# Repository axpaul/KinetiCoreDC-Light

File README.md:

# KinetiCoreDC Light

🌐 **Langue / Language :** [🇫🇷 Français](README.md) | [🇬🇧 English](README.en.md)

---

**KinetiCoreDC Light** est la **version minimale et compacte** du contrôleur de moteur DC durci **[KinetiCoreDC](https://github.com/axpaul/KinetiCoreDC)**. Conçue pour réduire au maximum l'encombrement PCB et le coût de nomenclature (BOM), cette variante conserve l'étage de puissance protégé, le pont en H `DRV8874`, les entrées de commande opto-isolées et le retour d'encodeur incrémental, tout en supprimant les bus périphériques encombrants de la version complète. Développé par **Paul Miailhe** pour **Berry Rocket**.

© 2025/2026 - **Paul Miailhe** (*Berry Rocket*).  
This material is licensed under the **CERN Open Hardware Licence Version 2 - Strongly Reciprocal (CERN-OHL-S)**. $\rightarrow$ [LICENSE](LICENSE)

---

## 1. Différences avec le dépôt officiel `KinetiCoreDC`

Cette édition **Light** cible les intégrations embarquées à fort contrainte de volume où un pilotage PWM/RC local avec retour incrémental suffit :

| Fonction / Bloc | [KinetiCoreDC (Officiel)](https://github.com/axpaul/KinetiCoreDC) | KinetiCoreDC Light (Ce dépôt) |
| :--- | :---: | :---: |
| **Protection alim (`LTC4365` + 2× `SiS412DN`) & LDO `3,3 V`** | ✅ Inclus | ✅ **Conservé** |
| **Driver moteur `DRV8874PWPR` ($6\text{ A}$ crête) + mesure `IPROPI`** | ✅ Inclus | ✅ **Conservé** |
| **Entrées opto-isolées PWM / GPIO (`2× TLP2310`)** | ✅ Inclus | ✅ **Conservé** (voie principale + redondante) |
| **Encodeur quadrature incrémental A/B (`TIM3` + Schmitt)** | ✅ Inclus | ✅ **Conservé** |
| **Fins de course (`2×` contact sec filtré + Schmitt)** | ✅ Inclus | ✅ **Conservé** |
| **Debug SWD + UART VCP (`Tag-Connect TC2070`)** | ✅ Inclus | ✅ **Conservé** |
| **IHM embarquée (LED RGB, buzzer piézo, LEDs sens moteur)** | ✅ Inclus | ✅ **Conservé** |
| **Sortie puissance moteur** | Connecteur `XT30PW-M` | 🔧 **Pads à souder directs** (`OUTA` / `OUTB`) |
| **Bus terrain différentiel RS-485 (`THVD1400D` + `SM712`)** | ✅ Inclus | ❌ **Retiré** (gain de surface PCB) |
| **Port capteur absolu SPI2 / I²C1 (`AS5047P` / `AS5600`)** | ✅ Inclus | ❌ **Retiré** (gain de surface PCB) |

---

## 2. Vue d'ensemble & Applications

Articulée autour d'un microcontrôleur **STM32G070CBT6** (ARM Cortex-M0+ @ $64\text{ MHz}$, horloge interne HSI) et d'un pont en H intégré **DRV8874PWPR**, la carte intègre l'essentiel de l'électronique de puissance, de protection et de conditionnement nécessaire au pilotage précis d'un actionneur DC :

- **Actionneur PWM / RC durci ou redondant :** Pilotage par consigne PWM ou impulsion RC ($1\text{–}2\text{ ms}$) via deux entrées opto-isolées (`TLP2310`) autorisant une voie de commande secondaire de secours.
- **Asservissement compact en boucle fermée :** Régulation PID en position, vitesse ou couple grâce au décodage quadrature matériel (`TIM3`), à la prise d'origine (*homing*) sur butées mécaniques et à la mesure de courant moteur (`IPROPI`).

---

## 3. Caractéristiques électriques

L'étage d'entrée est dimensionné pour une alimentation sur batterie **LiPo 2S ou 3S** (ou source DC régulée). Un contrôleur **LTC4365TS8** associé à deux MOSFETs N-Channel tête-bêche (**SiS412DN**) assure la coupure matérielle en cas de sous-tension, surtension ou inversion de polarité, tandis qu'une diode TVS **SMBJ15CA** protège le régulateur $+3{,}3\text{ V}$ contre les transitoires.

| Paramètre | Symbole | Min | Typ | Max | Unité | Conditions / Notes |
| :--- | :--- | :---: | :---: | :---: | :---: | :--- |
| **Tension d'entrée** | $V_{\text{IN}}$ | $5{,}90$ | $7{,}4\text{–}11{,}1$ | **$14{,}75$** | $\text{V}$ | Compatible LiPo 2S ($8{,}4\text{ V}$) et 3S ($12{,}6\text{ V}$) |
| **Tenue inversion polarité** | $V_{\text{REV}}$ | **$-40$** | — | — | $\text{V}$ | Blocage par N-MOSFETs tête-bêche |
| **Seuil sous-tension (coupure)** | $V_{\text{UVLO}}$ | — | $5{,}90$ | — | $\text{V}$ | Enclenchement à $6{,}20\text{ V}$ (config. défaut) |
| **Seuil surtension (coupure)** | $V_{\text{OVLO}}$ | — | **$14{,}75$** | — | $\text{V}$ | Réarmement à $14{,}01\text{ V}$ (TVS `SMBJ15CA`) |
| **Courant moteur régulé** | $I_{\text{TRIP}}$ | — | **$2{,}6$** | **$2{,}6$** | $\text{A}$ | $V_{\text{REF}} = 2{,}50\text{ V}$, $R_{\text{IPROPI}} = 2{,}49\text{ k}\Omega$ |
| **Courant moteur crête** | $I_{\text{PEAK}}$ | — | — | **$6{,}0$** | $\text{A}$ | Limite silicium `DRV8874` |
| **Puissance d'entrée** | $P_{\text{IN}}$ | — | $32{,}8$ | $38{,}4$ | $\text{W}$ | À $I_{\text{TRIP}} = 2{,}6\text{ A}$ (jusqu'à $88{,}5\text{ W}$ crête à $6\text{ A}$) |
| **Rail logique** | $V_{\text{3V3}}$ | $3{,}28$ | $3{,}30$ | $3{,}32$ | $\text{V}$ | Précision $\pm 0{,}4\text{ \%}$ (`MCP1703A`, boîtier SOT-223) |
| **Courant disponible $+3{,}3\text{ V}$** | $I_{\text{OUT(3V3)}}$ | — | — | **$250$** | $\text{mA}$ | Total carte ($\approx 50\text{ mA}$) + encodeur externe |
| **Courant de veille** | $I_{\text{SHDN}}$ | — | — | **$< 10$** | $\mu\text{A}$ | Broche `SHDN_EXT` tirée à `GND` |

> **Ajustement des seuils :** La fenêtre de protection UVLO/OVLO peut être adaptée à un profil batterie spécifique (LiPo 2S dédié $6{,}45\text{–}10{,}84\text{ V}$, LiPo 3S dédié $9{,}15\text{–}14{,}28\text{ V}$ ou pile 9V) via le pont diviseur du `LTC4365` sur la feuille `Power.kicad_sch`. Le seuil de courant $I_{\text{TRIP}}$ est également ajustable jusqu'à $6\text{ A}$ via `R_IPROPI`.

---

## 4. Interfaces & Connectique

Toutes les entrées/sorties externes conservées bénéficient des mêmes protections contre les décharges électrostatiques (ESD), les inversions de câblage et le bruit de découpage moteur ($32\text{ kHz}$). Le départ d'alimentation $+3{,}3\text{ V}$ vers l'encodeur (`J10`) est protégé par une résistance série de $22\ \Omega$, tandis que les signaux logiques sont filtrés matériellement puis remis en forme par des triggers de Schmitt (**SN74LVC2G14DBV**).

| Connecteur | Interface | Signal / Protocole | Conditionnement & Protection | Compatibilité |
| :--- | :--- | :--- | :--- | :--- |
| **`J2`** | `XT30PW-M` (2 pts) | Puissance entrée $V_{\text{IN}}$ | TVS `SMBJ15CA`, N-MOSFETs `SiS412DN` | Batterie LiPo 2S–3S ($15\text{ A}$ cont.) |
| **`J3` / `J4`** | Pads à souder (`1×1`) | Sorties moteur `OUTA` / `OUTB` | LEDs antiparallèles sens/PWM ($2\text{ k}\Omega$) | Moteur DC à balais (fils directs) |
| **`J7` / `J8`** | `JST-GH` (2 pts) | $2\times$ PWM / GPIO isolés ($3{,}3\text{–}5\text{ V}$) | Optocoupleurs `TLP2310`, clamp inverse `SMF6.0A` | Consigne PWM/RC, voie redondante |
| **`J10`** | `JST-GH` (4 pts) | Encodeur quadrature A/B ($3{,}3\text{–}5\text{ V}$) | `USBLC6-2SC6`, $+3{,}3\text{ V}$ ($22\ \Omega$), RC ($160\text{ kHz}$) + Schmitt | Encodeurs incrémentaux à effet Hall |
| **`J11` / `J5`** | `JST-GH` (2 pts) | $2\times$ Fins de course (`TRIG1` / `TRIG2`) | Pull-up $2{,}2\text{ k}\Omega$, RC ($160\text{ Hz}$) + Schmitt | Butées mécaniques Min / Max |
| **`J9`** | `JST-GH` (3 pts) | Activation carte (`SHDN_EXT`) | Pull-up $510\text{ k}\Omega$ vers $V_{\text{IN}}$ (`LTC4365`) | Interrupteur marche / veille |
| **`J6`** | `JST-GH` (2 pts) | Sortie défaut alim (`NFAULT_EXT`) | Drain ouvert actif bas + $22\ \Omega$ (`LTC4365`) | Supervision système hôte |
| **`J1`** | `TC2070-NL` (14 pts) | SWD + NRST + UART VCP (`USART3`) | Empreinte sans composants (STDC14) | ST-LINK/V3 (flash & debug) |

---

## 5. Brochage MCU (`STM32G070CBT6` — LQFP48)

| Bloc fonctionnel | Signal | Broche | Périphérique | Fonction |
| :--- | :--- | :---: | :--- | :--- |
| **Driver Moteur** | `PH/IN2_MCU` | `PA8` (28) | `TIM1_CH1` | Direction (`PH`) ou PWM secondaire |
| | `EN/IN1_MCU` | `PA9` (29) | `TIM1_CH2` | PWM principale moteur ($32\text{ kHz}$) |
| | `NSLEEP_MCU` | `PC6` (30) | `GPIO_Output` | Activation / Veille du pont en H |
| | `PMODE_MCU` | `PC7` (31) | `GPIO_Output` | Mode `PH/EN` (`0`) ou `PWM` (`1`) |
| | `NFAULT_MCU` | `PA10` (32) | `GPIO_EXTI10` | Interruption défaut driver (front descendant) |
| | `IPROPI_MCU` | `PB10` (22) | `ADC1_IN11` | Lecture courant moteur ($1{,}13\text{ V/A}$, filtre RC) |
| **Supervision** | `ADC_VM` | `PB2` (21) | `ADC1_IN10` | Mesure tension d'entrée $V_M$ |
| **Encodeur** | `TIM_ENC_A` / `B` | `PA6` (17), `PA7` (18) | `TIM3_CH1/CH2` | Décodage quadrature matériel X4 |
| **Optocoupleurs** | `OPTO1_MCU` / `OPTO2_MCU` | `PB14` (26), `PB15` (27) | `TIM15_CH1/CH2` | Input Capture PWM / Consigne redondante |
| **Fins de course** | `TRIG1_MCU` / `TRIG2_MCU` | `PD2` (40), `PD3` (41) | `GPIO_EXTI2/EXTI3` | Interruptions butées (front montant) |
| **IHM** | `BLUE` / `RED` / `GREEN` | `PC13`, `PC14`, `PC15` | `GPIO_Output` | LED RGB 8 couleurs (anode commune, actif bas) |
| | `BUZZER_MCU` | `PA4` (15) | `TIM14_CH1` | Signal piézo PWM $4\text{ kHz}$ |
| **Debug** | `SWDIO` / `SWCLK` | `PA13` (35), `PA14` (36) | `SYS_SWD` | Programmation et débogage |
| | `VPC_TX` / `VPC_RX` | `PA5` (16), `PB0` (19) | `USART3_TX/RX` | Console série virtuelle de diagnostic |

---

## 6. Architecture KiCad & Structure du dépôt

Le projet est conçu sous **KiCad 10.0** autour d'une feuille racine et de trois sous-feuilles hiérarchiques allégées, accompagnées du fichier de configuration **STM32CubeMX** (`KinetiCoreDC.ioc`) :

```text
KinetiCoreDC-Light/
├── KinetiCoreDC.kicad_pro       # Projet KiCad 10.0
├── KinetiCoreDC.kicad_sch       # Feuille 1/4 : MCU STM32G070CBT6 & hiérarchie
├── Interface.kicad_sch          # Feuille 2/4 : Optocoupleurs, encodeur quadrature, butées
├── Power.kicad_sch              # Feuille 3/4 : LTC4365, LDO 3.3V, DRV8874, RGB, buzzer
├── Connector.kicad_sch          # Feuille 4/4 : XT30 entrée, pads moteur, JST-GH, Tag-Connect
├── KinetiCoreDC.kicad_pcb       # Routage PCB compact
├── KinetiCoreDC.ioc             # Configuration matérielle STM32CubeMX
├── Datasheet/                   # Fiches techniques des composants
├── lib/                         # Symboles, empreintes et modèles 3D locaux
├── README.md                    # Documentation française
├── README.en.md                 # Documentation anglaise
└── LICENSE                      # Licence CERN-OHL-S-2.0

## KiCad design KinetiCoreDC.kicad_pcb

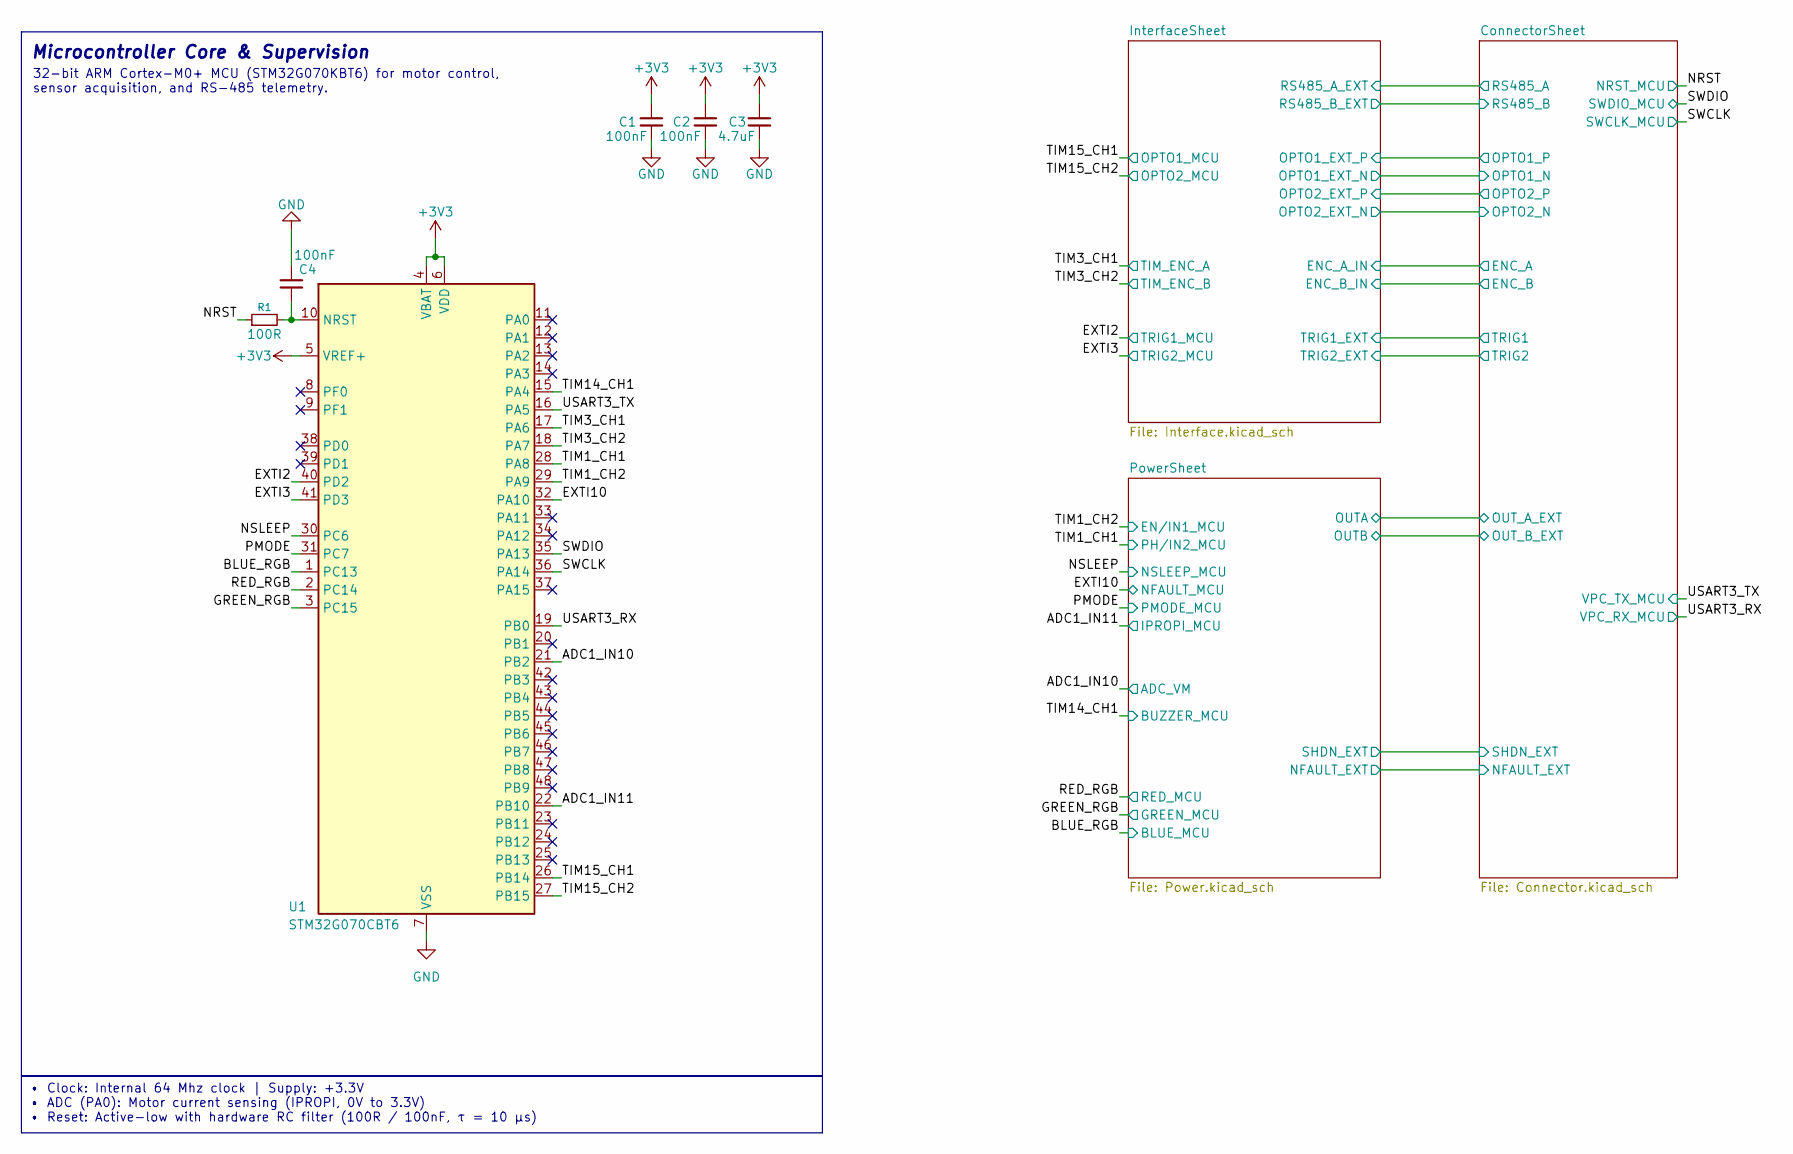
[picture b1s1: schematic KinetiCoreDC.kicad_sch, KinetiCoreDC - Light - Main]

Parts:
C1, C2, C4: 100nF; C_0603_1608Metric
C3: 4.7uF; C_0603_1608Metric
R1: 100R; R_0603_1608Metric
U1: STM32G070CBT6; LQFP-48_7x7mm_P0.5mm

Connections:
+3V3: C1.1, C2.1, C3.1, U1.4 (VBAT), U1.5 (VREF+), U1.6 (VDD); also elsewhere on the board
/ADC1_IN10: U1.21 (PB2); also elsewhere on the board
/ADC1_IN11: U1.22 (PB10); also elsewhere on the board
/BLUE_RGB: U1.1 (PC13); also elsewhere on the board
/EXTI2: U1.40 (PD2); also elsewhere on the board
/EXTI3: U1.41 (PD3); also elsewhere on the board
/EXTI10: U1.32 (PA10); also elsewhere on the board
/GREEN_RGB: U1.3 (PC15); also elsewhere on the board
/NRST: R1.1; also elsewhere on the board
/NSLEEP: U1.30 (PC6); also elsewhere on the board
/PMODE: U1.31 (PC7); also elsewhere on the board
/RED_RGB: U1.2 (PC14); also elsewhere on the board
/SWCLK: U1.36 (PA14); also elsewhere on the board
/SWDIO: U1.35 (PA13); also elsewhere on the board
/TIM1_CH1: U1.28 (PA8); also elsewhere on the board
/TIM1_CH2: U1.29 (PA9); also elsewhere on the board
/TIM3_CH1: U1.17 (PA6); also elsewhere on the board
/TIM3_CH2: U1.18 (PA7); also elsewhere on the board
/TIM14_CH1: U1.15 (PA4); also elsewhere on the board
/TIM15_CH1: U1.26 (PB14); also elsewhere on the board
/TIM15_CH2: U1.27 (PB15); also elsewhere on the board
/USART3_RX: U1.19 (PB0); also elsewhere on the board
/USART3_TX: U1.16 (PA5); also elsewhere on the board
GND: C1.2, C2.2, C3.2, C4.2, U1.7 (VSS); also elsewhere on the board
unnamed: C4.1, R1.2, U1.10 (NRST)

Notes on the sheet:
Microcontroller Core & Supervision
32-bit ARM Cortex-M0+ MCU (STM32G070KBT6) for motor control, sensor acquisition, and RS-485 telemetry.
• Clock: Internal 64 Mhz clock | Supply: +3.3V • ADC (PA0): Motor current sensing (IPROPI, 0V to 3.3V) • Reset: Active-low with hardware RC filter (100R / 100nF, τ = 10 µs)

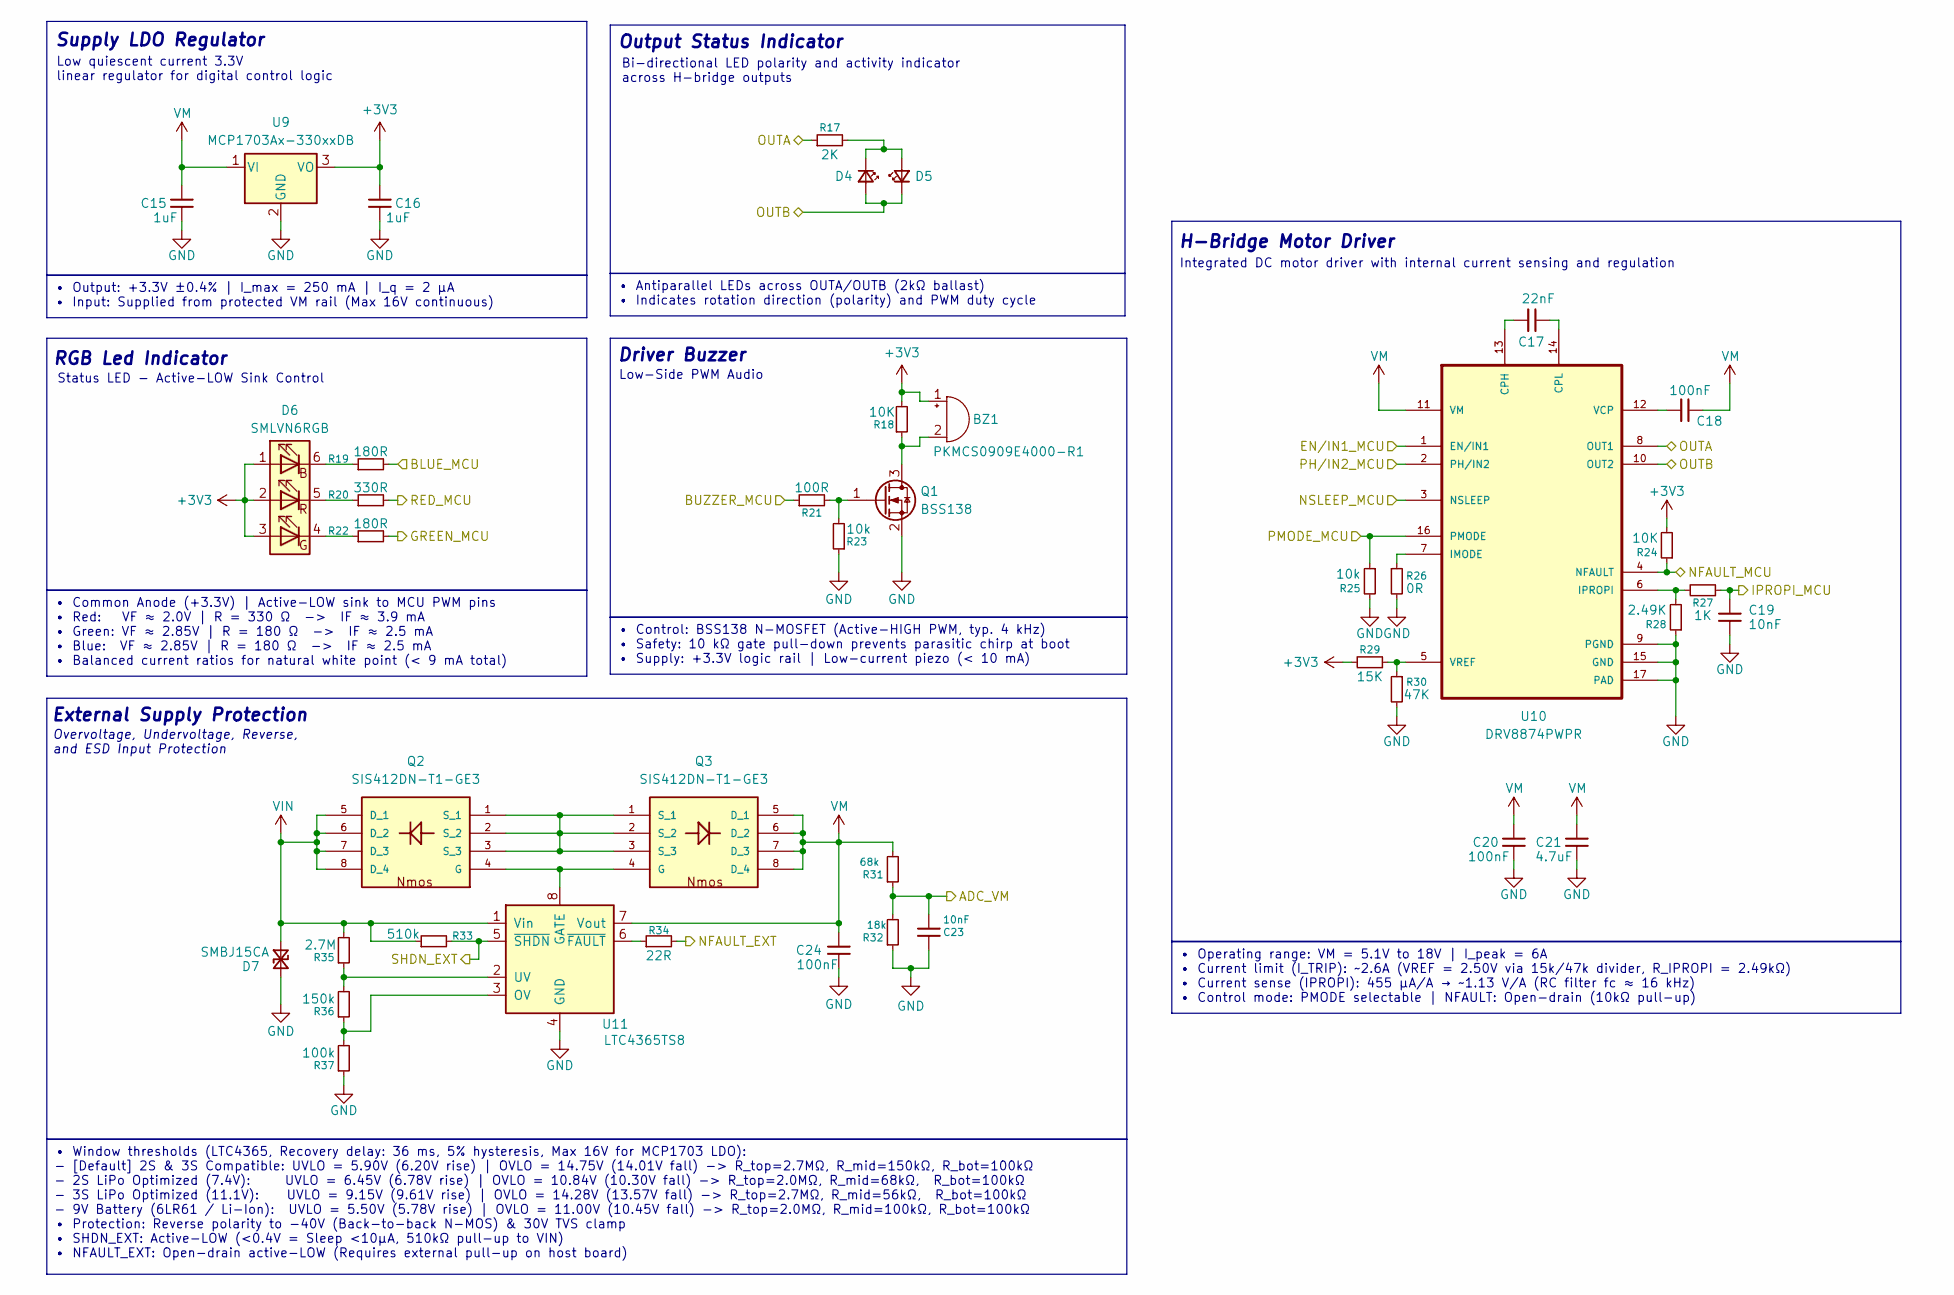
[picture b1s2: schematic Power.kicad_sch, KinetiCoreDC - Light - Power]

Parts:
BZ1: PKMCS0909E4000-R1; Buzzer_Murata_PKMCS0909E
C15, C16: 1uF; C_0805_2012Metric
C17: 22nF; C_0603_1608Metric
C18, C24: 100nF; C_0603_1608Metric
C19, C23: 10nF; C_0603_1608Metric
C20: 100nF; C_0805_2012Metric
C21: 4.7uF; C_0805_2012Metric
D4, D5: LED_Small; LED_0603_1608Metric
D6: SMLVN6RGB; LED_ROHM_SMLVN6
D7: SMBJ15CA; D_SMA
Q1: BSS138; SOT-23
Q2, Q3: SIS412DN-T1-GE3; POWERPAK-1212-8; MOUSER_PART_NUMBER 781-SIS412DN-T1-GE3
R17: 2K; R_0603_1608Metric
R18, R24: 10K; R_0603_1608Metric
R19, R22: 180R; R_0603_1608Metric
R20: 330R; R_0603_1608Metric
R21: 100R; R_0603_1608Metric
R23, R25: 10k; R_0603_1608Metric
R26: 0R; R_0603_1608Metric
R27: 1K; R_0603_1608Metric
R28: 2.49K; R_0603_1608Metric
R29: 15K; R_0603_1608Metric
R30: 47K; R_0603_1608Metric
R31: 68k; R_0603_1608Metric
R32: 18k; R_0603_1608Metric
R33: 510k; R_0603_1608Metric
R34: 22R; R_0603_1608Metric
R35: 2.7M; R_0603_1608Metric
R36: 150k; R_0603_1608Metric
R37: 100k; R_0603_1608Metric
U9: MCP1703Ax-330xxDB; SOT-223-3_TabPin2
U10: DRV8874PWPR; SOP65P640X120-17N
U11: LTC4365TS8; TSOT-23-8

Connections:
+3V3: BZ1.1 (+), C16.1, D6.1 (BA), D6.2 (RA), D6.3 (GA), R18.2, R24.2, R29.2, U9.3 (VO); also elsewhere on the board
/ADC1_IN10: C23.2, R31.1, R32.2; also elsewhere on the board
/ADC1_IN11: C19.2, R27.1; also elsewhere on the board
/BLUE_RGB: R19.2; also elsewhere on the board
/ConnectorSheet/NFAULT_EXT: R34.2; also elsewhere on the board
/ConnectorSheet/OUT_A_EXT: R17.1, U10.8 (OUT1); also elsewhere on the board
/ConnectorSheet/OUT_B_EXT: D4.2 (A), D5.1 (K), U10.10 (OUT2); also elsewhere on the board
/ConnectorSheet/SHDN_EXT: R33.2, U11.5 (~SHDN); also elsewhere on the board
/EXTI10: R24.1, U10.4 (NFAULT); also elsewhere on the board
/GREEN_RGB: R22.2; also elsewhere on the board
/NSLEEP: U10.3 (NSLEEP); also elsewhere on the board
/PMODE: R25.1, U10.16 (PMODE); also elsewhere on the board
/RED_RGB: R20.2; also elsewhere on the board
/TIM1_CH1: U10.2 (PH/IN2); also elsewhere on the board
/TIM1_CH2: U10.1 (EN/IN1); also elsewhere on the board
/TIM14_CH1: R21.1; also elsewhere on the board
GND: C15.2, C16.2, C19.1, C20.2, C21.2, C23.1, C24.2, D7.2 (A2), Q1.2 (S), R23.1, R25.2, R26.2, R28.1, R30.2, R32.1, R37.1, U9.2 (GND), U10.9 (PGND), U10.15 (GND), U10.17 (PAD), U11.4 (GND); also elsewhere on the board
unnamed: BZ1.2 (-), Q1.3 (D), R18.1
unnamed: D4.1 (K), D5.2 (A), R17.2
unnamed: D6.6 (BK), R19.1
unnamed: D6.4 (GK), R22.1
unnamed: D6.5 (RK), R20.1
unnamed: Q1.1 (G), R21.2, R23.2
unnamed: Q2.4 (G), Q3.4 (G), U11.8 (GATE)
unnamed: Q2.1 (S_1), Q2.2 (S_2), Q2.3 (S_3), Q3.1 (S_1), Q3.2 (S_2), Q3.3 (S_3)
unnamed: C17.1, U10.13 (CPH)
unnamed: C17.2, U10.14 (CPL)
unnamed: R26.1, U10.7 (IMODE)
unnamed: R27.2, R28.2, U10.6 (IPROPI)
unnamed: C18.1, U10.12 (VCP)
unnamed: R29.1, R30.1, U10.5 (VREF)
unnamed: R36.1, R37.2, U11.3 (OV)
unnamed: R35.1, R36.2, U11.2 (UV)
unnamed: R34.1, U11.6 (~FAULT)
VIN: D7.1 (A1), Q2.5 (D_1), Q2.6 (D_2), Q2.7 (D_3), Q2.8 (D_4), R33.1, R35.2, U11.1 (Vin); also elsewhere on the board
VM: C15.1, C18.2, C20.1, C21.1, C24.1, Q3.5 (D_1), Q3.6 (D_2), Q3.7 (D_3), Q3.8 (D_4), R31.2, U9.1 (VI), U10.11 (VM), U11.7 (Vout)

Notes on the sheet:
H-Bridge Motor Driver
RGB Led Indicator
Low quiescent current 3.3V linear regulator for digital control logic
Low-Side PWM Audio
Output Status Indicator
Driver Buzzer
Supply LDO Regulator
Overvoltage, Undervoltage, Reverse, and ESD Input Protection
Integrated DC motor driver with internal current sensing and regulation
External Supply Protection
Bi-directional LED polarity and activity indicator across H-bridge outputs
Status LED - Active-LOW Sink Control
• Control: BSS138 N-MOSFET (Active-HIGH PWM, typ. 4 kHz) • Safety: 10 kΩ gate pull-down prevents parasitic chirp at boot • Supply: +3.3V logic rail | Low-current piezo (< 10 mA)
• Window thresholds (LTC4365, Recovery delay: 36 ms, 5% hysteresis, Max 16V for MCP1703 LDO): - [Default] 2S & 3S Compatible: UVLO = 5.90V (6.20V rise) | OVLO = 14.75V (14.01V fall) -> R_top=2.7MΩ, R_mid=150kΩ, R_bot=100kΩ - 2S LiPo Optimized (7.4V): UVLO = 6.45V (6.78V rise) | OVLO = 10.84V (10.30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
• Output: +3.3V ±0.4% | I_max = 250 mA | I_q = 2 µA • Input: Supplied from protected VM rail (Max 16V continuous)
• Antiparallel LEDs across OUTA/OUTB (2kΩ ballast) • Indicates rotation direction (polarity) and PWM duty cycle
• Operating range: VM = 5.1V to 18V | I_peak = 6A • Current limit (I_TRIP): ~2.6A (VREF = 2.50V via 15k/47k divider, R_IPROPI = 2.49kΩ) • Current sense (IPROPI): 455 µA/A → ~1.13 V/A (RC filter fc ≈ 16 kHz) • Control mode: PMODE selectable | NFAULT: Open-drain (10kΩ pull-up)
• Common Anode (+3.3V) | Active-LOW sink to MCU PWM pins • Red: VF ≈ 2.0V | R = 330 Ω -> IF ≈ 3.9 mA • Green: VF ≈ 2.85V | R = 180 Ω -> IF ≈ 2.5 mA • Blue: VF ≈ 2.85V | R = 180 Ω -> IF ≈ 2.5 mA • Balanced current ratios for natural white point (< 9 mA total)

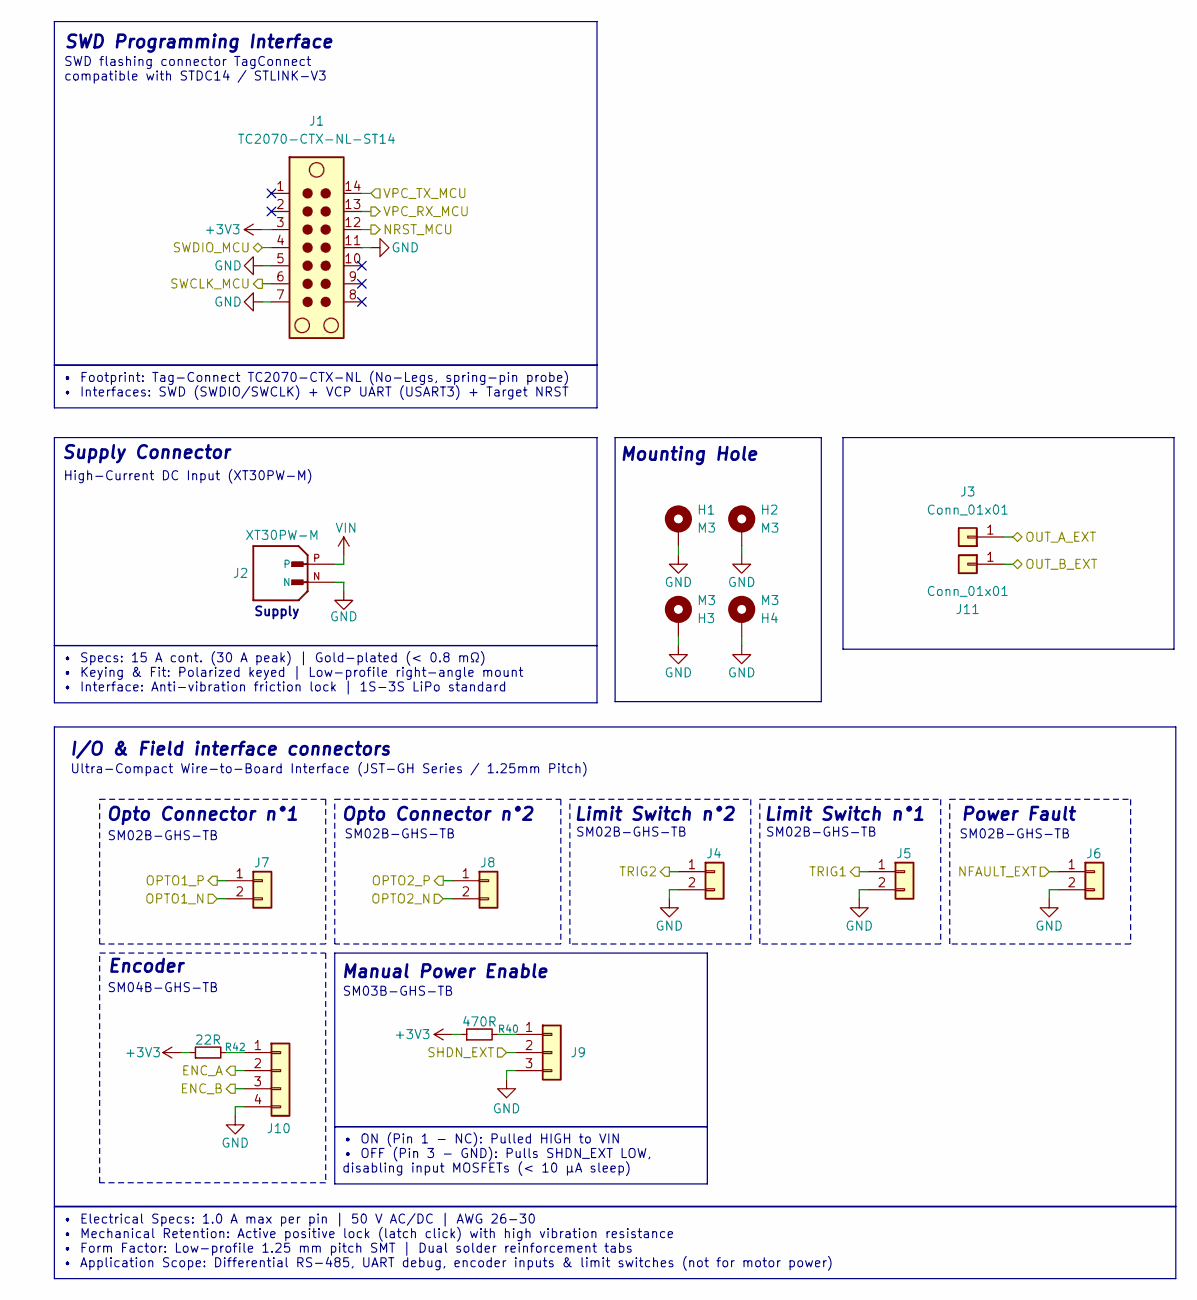
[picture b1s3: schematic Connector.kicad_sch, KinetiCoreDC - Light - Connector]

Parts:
H1, H2, H3, H4: M3; MountingHole_3.2mm_M3_DIN965_Pad_TopBottom
J1: TC2070-CTX-NL-ST14; Tag-Connect_TC2070-IDC-FP_2x07_P1.27mm_Vertical
J2: XT30PW-M; AMASS_XT30PW-M; PARTREV 1.2
J3, J11: Conn_01x01; SolderWirePad_1x01_SMD_4x8mm
J4, J5, J6, J7: SM02B-GHS-TB; JST_GH_SM02B-GHS-TB_1x02-1MP_P1.25mm_Horizontal
J8: BM02B-GHS-TBT; JST_GH_SM02B-GHS-TB_1x02-1MP_P1.25mm_Horizontal
J9: SM03B-GHS-TB; JST_GH_SM03B-GHS-TB_1x03-1MP_P1.25mm_Horizontal
J10: SM04B-GHS-TB; JST_GH_SM04B-GHS-TB_1x04-1MP_P1.25mm_Horizontal
R40: 470R; R_0603_1608Metric
R42: 22R; R_0603_1608Metric

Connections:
+3V3: J1.3, R40.1, R42.1; also elsewhere on the board
/ConnectorSheet/ENC_A: J10.2; also elsewhere on the board
/ConnectorSheet/ENC_B: J10.3; also elsewhere on the board
/ConnectorSheet/NFAULT_EXT: J6.1; also elsewhere on the board
/ConnectorSheet/OPTO1_N: J7.2; also elsewhere on the board
/ConnectorSheet/OPTO1_P: J7.1; also elsewhere on the board
/ConnectorSheet/OPTO2_N: J8.2; also elsewhere on the board
/ConnectorSheet/OPTO2_P: J8.1; also elsewhere on the board
/ConnectorSheet/OUT_A_EXT: J3.1 (Pin_1_1); also elsewhere on the board
/ConnectorSheet/OUT_B_EXT: J11.1 (Pin_1_1); also elsewhere on the board
/ConnectorSheet/SHDN_EXT: J9.2; also elsewhere on the board
/ConnectorSheet/TRIG1: J5.1; also elsewhere on the board
/ConnectorSheet/TRIG2: J4.1; also elsewhere on the board
/NRST: J1.12; also elsewhere on the board
/SWCLK: J1.6; also elsewhere on the board
/SWDIO: J1.4; also elsewhere on the board
/USART3_RX: J1.13; also elsewhere on the board
/USART3_TX: J1.14; also elsewhere on the board
GND: H1.1 (1_1), H2.1 (1_1), H3.1 (1_1), H4.1 (1_1), J1.5, J1.7, J1.11, J2.N, J4.2, J5.2, J6.2, J9.3, J10.4; also elsewhere on the board
unnamed: J9.1, R40.2
unnamed: J10.1, R42.2
VIN: J2.P; also elsewhere on the board

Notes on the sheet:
Limit Switch n°1
Encoder
Power Fault
I/O & Field interface connectors
SM03B-GHS-TB
Opto Connector n°1
High-Current DC Input (XT30PW-M)
SM02B-GHS-TB
SWD flashing connector TagConnect compatible with STDC14 / STLINK-V3
Limit Switch n°2
Opto Connector n°2
Mounting Hole
SM04B-GHS-TB
Manual Power Enable
Ultra-Compact Wire-to-Board Interface (JST-GH Series / 1.25mm Pitch)
Supply Connector
SWD Programming Interface
Supply
• Footprint: Tag-Connect TC2070-CTX-NL (No-Legs, spring-pin probe) • Interfaces: SWD (SWDIO/SWCLK) + VCP UART (USART3) + Target NRST
• Electrical Specs: 1.0 A max per pin | 50 V AC/DC | AWG 26-30 • Mechanical Retention: Active positive lock (latch click) with high vibration resistance • Form Factor: Low-profile 1.25 mm pitch SMT | Dual solder reinforcement tabs • Application Scope: Differential RS-485, UART debug, encoder inputs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
• Specs: 15 A cont. (30 A peak) | Gold-plated (< 0.8 mΩ) • Keying & Fit: Polarized keyed | Low-profile right-angle mount • Interface: Anti-vibration friction lock | 1S-3S LiPo standard
• ON (Pin 1 - NC): Pulled HIGH to VIN • OFF (Pin 3 - GND): Pulls SHDN_EXT LOW, disabling input MOSFETs (< 10 µA sleep)

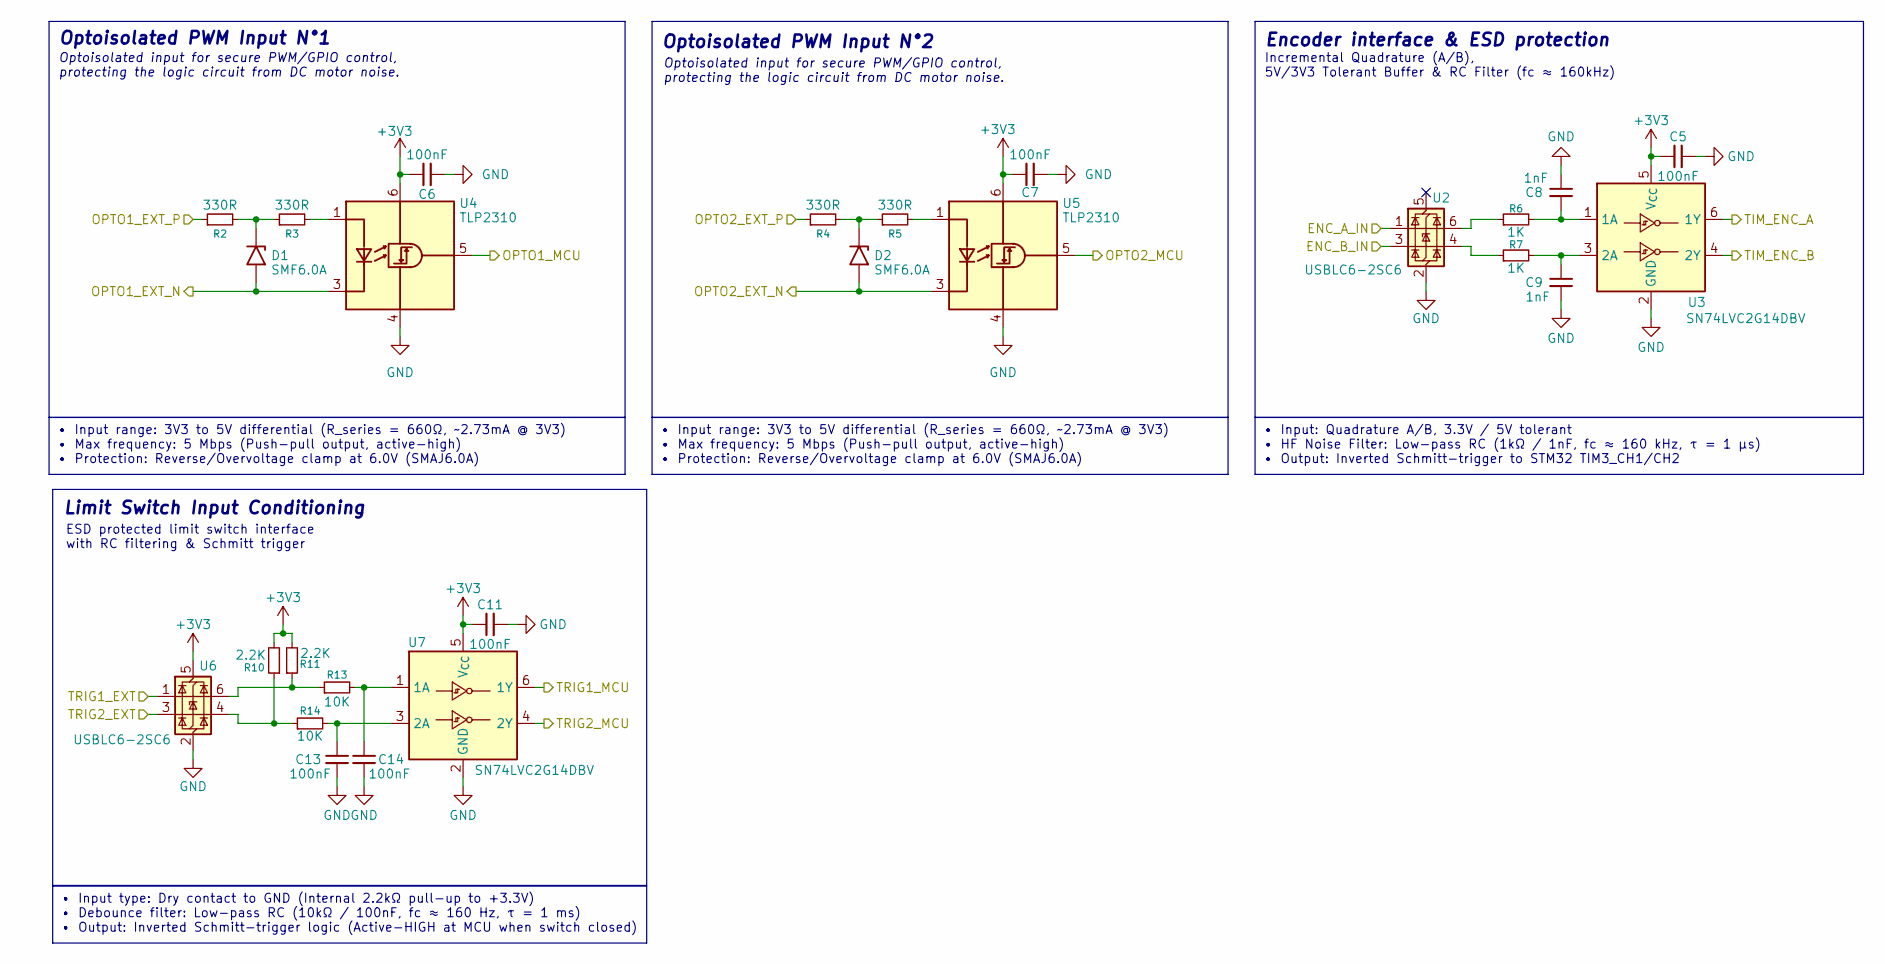
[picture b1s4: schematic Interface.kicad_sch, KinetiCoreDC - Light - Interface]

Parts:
C5, C6, C7, C11, C13, C14: 100nF; C_0603_1608Metric
C8, C9: 1nF; C_0603_1608Metric
D1, D2: SMF6.0A; D_SOD-123F
R2, R3, R4, R5: 330R; R_0603_1608Metric
R6, R7: 1K; R_0603_1608Metric
R10, R11: 2.2K; R_0603_1608Metric
R13, R14: 10K; R_0603_1608Metric
U2, U6: USBLC6-2SC6; SOT-23-6
U3, U7: SN74LVC2G14DBV; SOT-23-6
U4, U5: TLP2310; SO-5-6_4.55x3.7mm_P1.27mm

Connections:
+3V3: C5.1, C6.1, C7.1, C11.1, R10.2, R11.2, U3.5 (V_{CC}), U4.6 (VDD), U5.6 (VDD), U6.5 (VBUS), U7.5 (V_{CC}); also elsewhere on the board
/ConnectorSheet/ENC_A: U2.1 (I/O1); also elsewhere on the board
/ConnectorSheet/ENC_B: U2.3 (I/O2); also elsewhere on the board
/ConnectorSheet/OPTO1_N: D1.2 (A2), U4.3 (K); also elsewhere on the board
/ConnectorSheet/OPTO1_P: R2.1; also elsewhere on the board
/ConnectorSheet/OPTO2_N: D2.2 (A2), U5.3 (K); also elsewhere on the board
/ConnectorSheet/OPTO2_P: R4.1; also elsewhere on the board
/ConnectorSheet/TRIG1: U6.1 (I/O1); also elsewhere on the board
/ConnectorSheet/TRIG2: U6.3 (I/O2); also elsewhere on the board
/EXTI2: U7.6 (1Y); also elsewhere on the board
/EXTI3: U7.4 (2Y); also elsewhere on the board
/TIM3_CH1: U3.6 (1Y); also elsewhere on the board
/TIM3_CH2: U3.4 (2Y); also elsewhere on the board
/TIM15_CH1: U4.5 (VO); also elsewhere on the board
/TIM15_CH2: U5.5 (VO); also elsewhere on the board
GND: C5.2, C6.2, C7.2, C8.1, C9.1, C11.2, C13.1, C14.1, U2.2 (GND), U3.2 (GND), U4.4 (GND), U5.4 (GND), U6.2 (GND), U7.2 (GND); also elsewhere on the board
unnamed: D1.1 (A1), R2.2, R3.1
unnamed: D2.1 (A1), R4.2, R5.1
unnamed: R6.1, U2.6 (I/O1)
unnamed: R7.1, U2.4 (I/O2)
unnamed: R10.1, R14.1, U6.4 (I/O2)
unnamed: R11.1, R13.1, U6.6 (I/O1)
unnamed: C8.2, R6.2, U3.1 (1A)
unnamed: C9.2, R7.2, U3.3 (2A)
unnamed: R3.2, U4.1 (A)
unnamed: R5.2, U5.1 (A)
unnamed: C14.2, R13.2, U7.1 (1A)
unnamed: C13.2, R14.2, U7.3 (2A)

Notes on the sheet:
Optoisolated PWM Input N°1
Optoisolated input for secure PWM/GPIO control, protecting the logic circuit from DC motor noise.
Incremental Quadrature (A/B), 5V/3V3 Tolerant Buffer & RC Filter (fc ≈ 160kHz)
Encoder interface & ESD protection
Limit Switch Input Conditioning
ESD protected limit switch interface with RC filtering & Schmitt trigger
Optoisolated PWM Input N°2
• Input: Quadrature A/B, 3.3V / 5V tolerant • HF Noise Filter: Low-pass RC (1kΩ / 1nF, fc ≈ 160 kHz, τ = 1 µs) • Output: Inverted Schmitt-trigger to STM32 TIM3_CH1/CH2
• Input type: Dry contact to GND (Internal 2.2kΩ pull-up to +3.3V) • Debounce filter: Low-pass RC (10kΩ / 100nF, fc ≈ 160 Hz, τ = 1 ms) • Output: Inverted Schmitt-trigger logic (Active-HIGH at MCU when switch closed)
• Input range: 3V3 to 5V differential (R_series = 660Ω, ~2.73mA @ 3V3) • Max frequency: 5 Mbps (Push-pull output, active-high) • Protection: Reverse/Overvoltage clamp at 6.0V (SMAJ6.0A)

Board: 4 copper layers, 90 parts (6 on the bottom side), 70 nets, no tracks yet.

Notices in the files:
README.md:
License: CERN-OHL-S-2.0
